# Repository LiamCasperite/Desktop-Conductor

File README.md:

# DesktopConductor
## A personal desktop macropad to control media and audio playing on your computer.

#### DesktopConductor is one of my very first hardware projects and first time using HackClub softwars like lapse, hackatime, wakatime, and the stardance projects.
---
It consists of an oled screen which will in future iterations be adapted into a song display for the current song and artist, 3 keys for pause/play, back, and skip in media controll, and a rotary encoder which can be used to adjust the volume and pressed to mute and unmute.

Currently the firmware is basic and has not be made to include these features but they will be added and worked on after the prototype is first assembled and built.

## Here is a photo of the project rendered in fusion!

I struggled and aufull lot with 3d modeling and fusion since it was my very first experience as well as in KiCad where the 3d model of the PCB and components was challenging to acomplish.

## Here are some photos of the PCB, Schematic and more!

#### Forgive the messyness of the Schematic and the wiring, this is my first time ever using KiCAD
---

### **Bill Of Materials**
| **Component**                | **Qty** |
|------------------------------|---------|
| **XIAO RP2040**              | 1       |
| **EC11 Rotary Encoder**      | 1       |
| **Cherry MX Switches**       | 3       |
| **PCB**                      | 1       |
| **M3x16mm screws**           | 4       |
| **M3x5mx4mm heatset inserts**| 4       |
| **white blank DSA keycaps**  | 3       |

## Others
| **Component**              | **Qty** |
|----------------------------|---------|
| **Case Top.stl**           | 9       |
| **Case Bottom.stl**        | 1       |
| **firmware.txt (CircuitPython)** | 1       |

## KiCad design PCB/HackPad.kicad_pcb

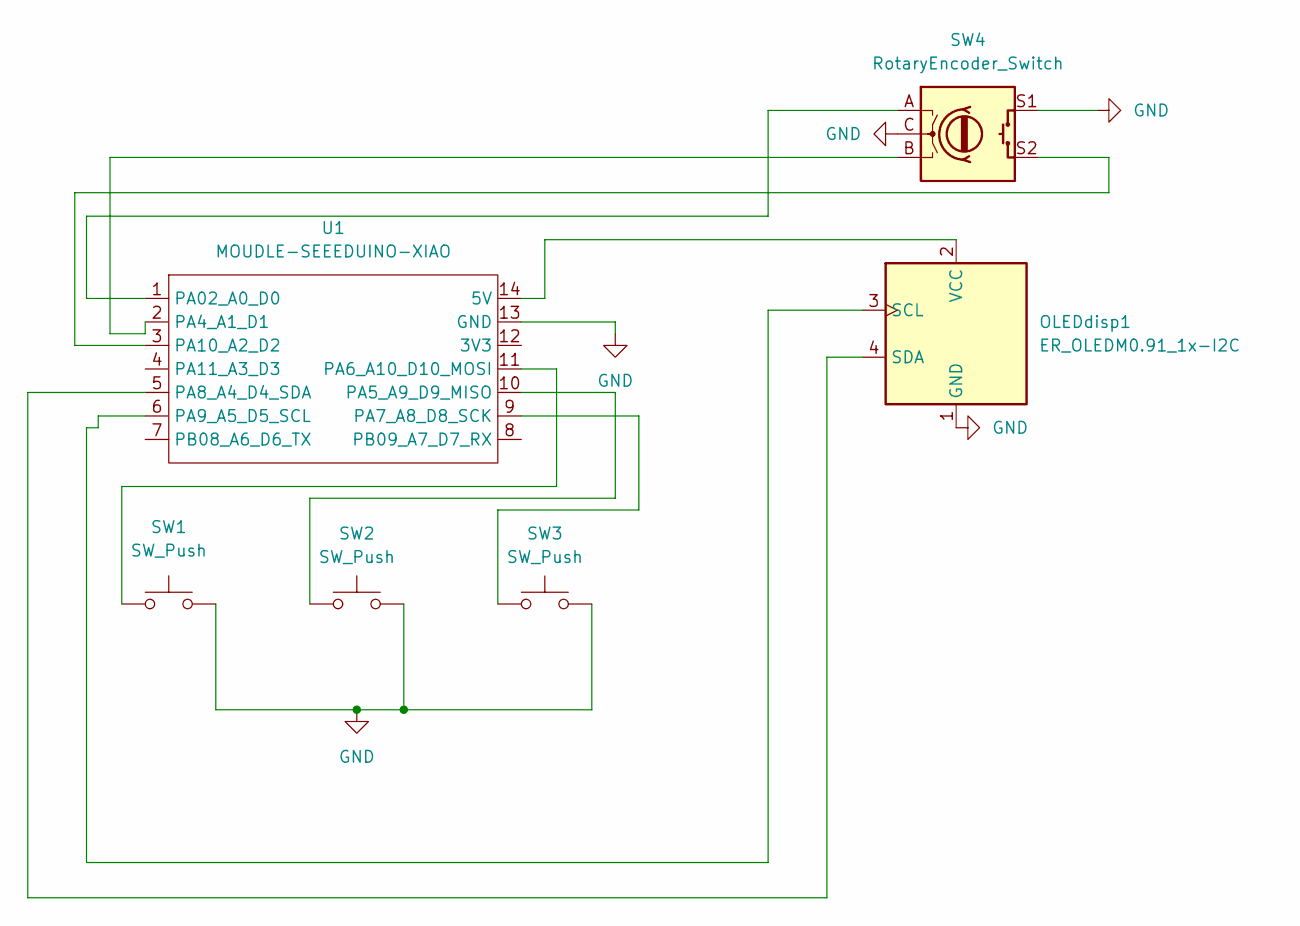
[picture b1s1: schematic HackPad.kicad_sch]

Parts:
OLEDdisp1: ER_OLEDM0.91_1x-I2C
SW1, SW2, SW3: SW_Push; SW_Cherry_MX_1.00u_PCB
SW4: RotaryEncoder_Switch; RotaryEncoder_Alps_EC11E-Switch_Vertical_H20mm
U1: MOUDLE-SEEEDUINO-XIAO; XIAO-Generic-Hybrid-14P-2.54-21X17.8MM

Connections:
GND: OLEDdisp1.1 (GND), SW1.2, SW2.2, SW3.2, SW4.C, SW4.S1, U1.13 (GND)
unnamed: OLEDdisp1.3 (SCL), U1.6 (PA9_A5_D5_SCL)
unnamed: OLEDdisp1.4 (SDA), U1.5 (PA8_A4_D4_SDA)
unnamed: OLEDdisp1.2 (VCC), U1.14 (5V)
unnamed: SW4.A, U1.1 (PA02_A0_D0)
unnamed: SW4.B, U1.2 (PA4_A1_D1)
unnamed: SW2.1, U1.10 (PA5_A9_D9_MISO)
unnamed: SW1.1, U1.11 (PA6_A10_D10_MOSI)
unnamed: SW3.1, U1.9 (PA7_A8_D8_SCK)
unnamed: SW4.S2, U1.3 (PA10_A2_D2)

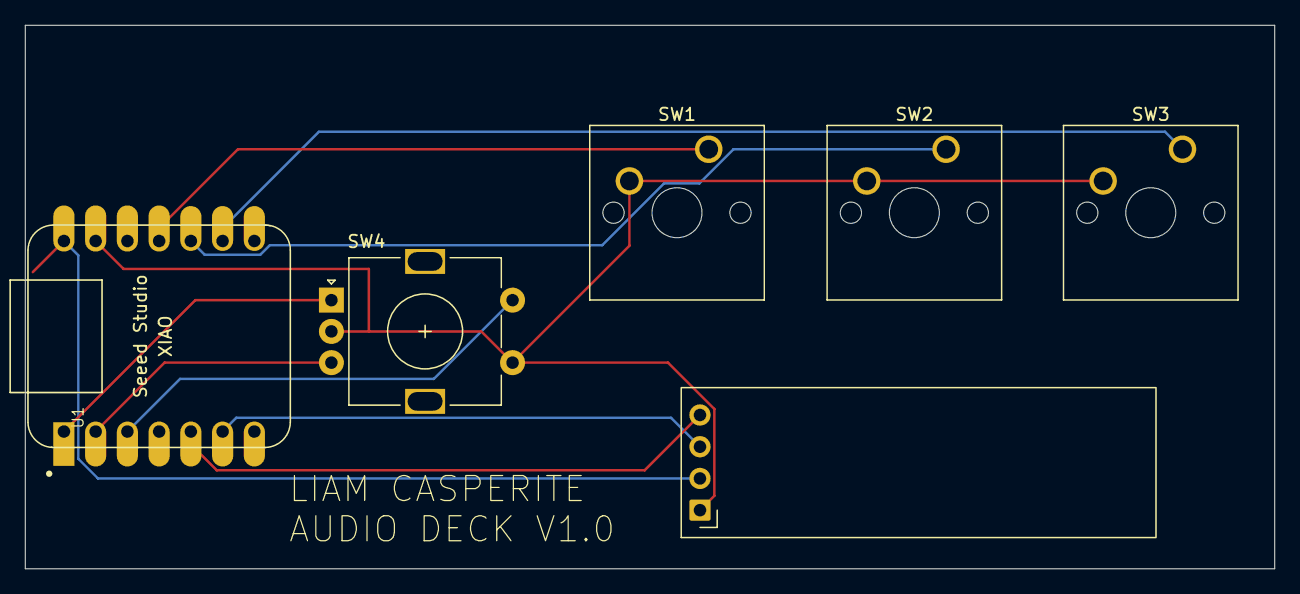
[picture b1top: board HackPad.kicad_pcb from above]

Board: 2 copper layers, 100.0 x 43.5 mm, 6 parts (0 on the bottom side), 10 nets.
